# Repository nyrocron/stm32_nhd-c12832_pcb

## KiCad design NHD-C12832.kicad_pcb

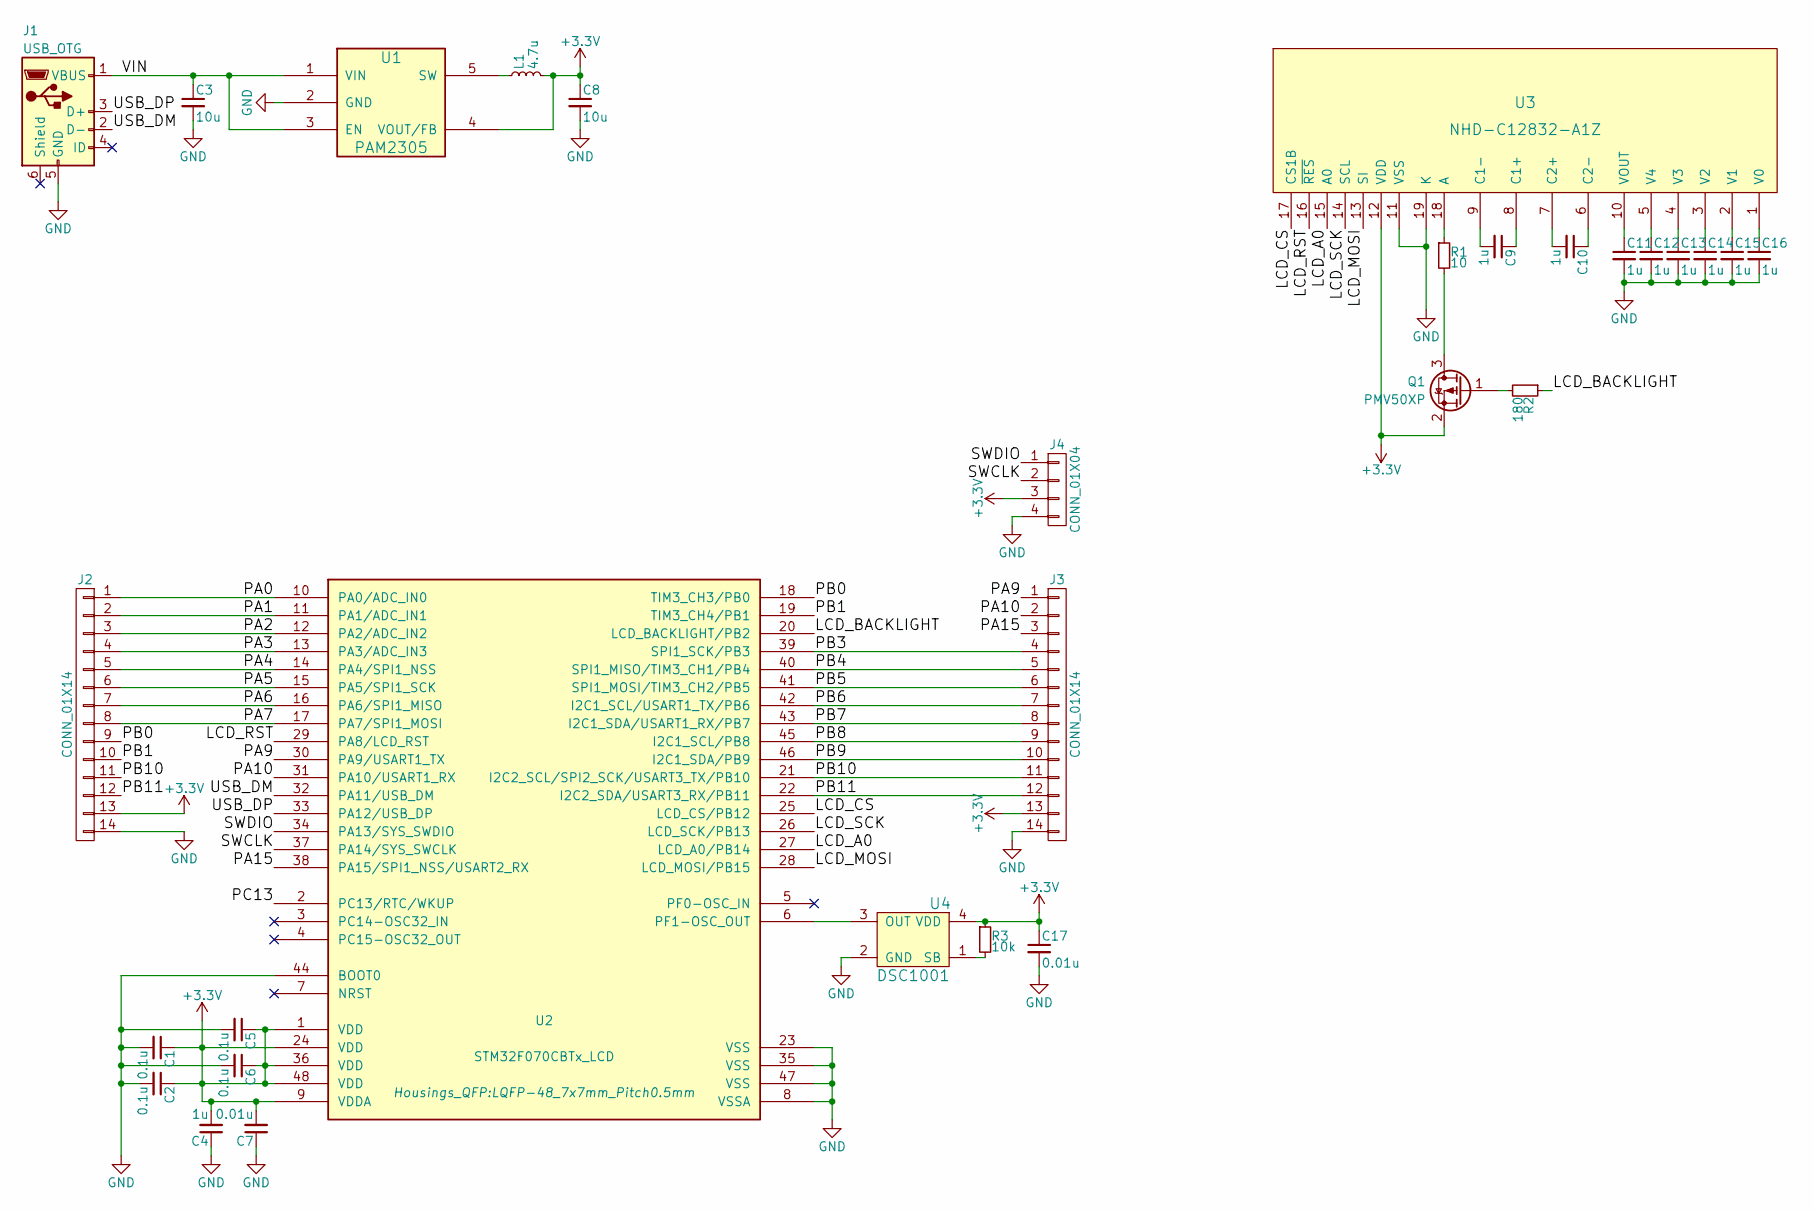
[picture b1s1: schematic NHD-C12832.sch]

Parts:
C1, C2, C5, C6: 0.1u; C_0603
C3, C8: 10u; C_0805
C4, C9, C10, C11, C12, C13, C14, C15, C16: 1u; C_0603
C7, C17: 0.01u; C_0603
J1: USB_OTG; USB_Micro-B_surface2
J2, J3: CONN_01X14; SOLDERPADS_14
J4: CONN_01X04; JST-SH_SM04B
L1: 4.7u; C_0805
Q1: PMV50XP; SOT-23
R1: 10; R_0603
R2: 180; R_0603
R3: 10k; R_0603
U1: PAM2305; SOT-23-5
U2: STM32F070CBTx_LCD; LQFP-48_7x7mm_Pitch0.5mm
U3: NHD-C12832-A1Z; NHD-C12832
U4: DSC1001; Crystal_SMD_5032-4pin_5.0x3.2mm

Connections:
+3V3: C1.1, C2.1, C4.2, C5.1, C6.1, C7.2, C8.1, C17.1, J2.13, J3.13, J4.3, L1.2, Q1.2 (S), R3.1, U1.4 (VOUT/FB), U2.1 (VDD), U2.9 (VDDA), U2.24 (VDD), U2.36 (VDD), U2.48 (VDD), U3.12 (VDD), U4.4 (VDD)
/LCD_A0: U2.27 (LCD_A0/PB14), U3.15 (A0)
/LCD_BACKLIGHT: R2.1, U2.20 (LCD_BACKLIGHT/PB2)
/LCD_CS: U2.25 (LCD_CS/PB12), U3.17 (CS1B)
/LCD_MOSI: U2.28 (LCD_MOSI/PB15), U3.13 (SI)
/LCD_RST: U2.29 (PA8/LCD_RST), U3.16 (~RES)
/LCD_SCK: U2.26 (LCD_SCK/PB13), U3.14 (SCL)
/PA0: J2.1, U2.10 (PA0/ADC_IN0)
/PA1: J2.2, U2.11 (PA1/ADC_IN1)
/PA2: J2.3, U2.12 (PA2/ADC_IN2)
/PA3: J2.4, U2.13 (PA3/ADC_IN3)
/PA4: J2.5, U2.14 (PA4/SPI1_NSS)
/PA5: J2.6, U2.15 (PA5/SPI1_SCK)
/PA6: J2.7, U2.16 (PA6/SPI1_MISO)
/PA7: J2.8, U2.17 (PA7/SPI1_MOSI)
/PA9: J3.1, U2.30 (PA9/USART1_TX)
/PA10: J3.2, U2.31 (PA10/USART1_RX)
/PA15: J3.3, U2.38 (PA15/SPI1_NSS/USART2_RX)
/PB0: J2.9, U2.18 (TIM3_CH3/PB0)
/PB1: J2.10, U2.19 (TIM3_CH4/PB1)
/PB3: J3.4, U2.39 (SPI1_SCK/PB3)
/PB4: J3.5, U2.40 (SPI1_MISO/TIM3_CH1/PB4)
/PB5: J3.6, U2.41 (SPI1_MOSI/TIM3_CH2/PB5)
/PB6: J3.7, U2.42 (I2C1_SCL/USART1_TX/PB6)
/PB7: J3.8, U2.43 (I2C1_SDA/USART1_RX/PB7)
/PB8: J3.9, U2.45 (I2C1_SCL/PB8)
/PB9: J3.10, U2.46 (I2C1_SDA/PB9)
/PB10: J2.11, J3.11, U2.21 (I2C2_SCL/SPI2_SCK/USART3_TX/PB10)
/PB11: J2.12, J3.12, U2.22 (I2C2_SDA/USART3_RX/PB11)
/SWCLK: J4.2, U2.37 (PA14/SYS_SWCLK)
/SWDIO: J4.1, U2.34 (PA13/SYS_SWDIO)
/USB_DM: J1.2 (D-), U2.32 (PA11/USB_DM)
/USB_DP: J1.3 (D+), U2.33 (PA12/USB_DP)
/VIN: C3.1, J1.1 (VBUS), U1.1 (VIN), U1.3 (EN)
GND: C1.2, C2.2, C3.2, C4.1, C5.2, C6.2, C7.1, C8.2, C11.2, C12.2, C13.2, C14.2, C15.2, C16.2, C17.2, J1.5 (GND), J2.14, J3.14, J4.4, U1.2 (GND), U2.8 (VSSA), U2.23 (VSS), U2.35 (VSS), U2.44 (BOOT0), U2.47 (VSS), U3.11 (VSS), U3.19 (K), U4.2 (GND)
unnamed: C9.1, U3.8 (C1+)
unnamed: C9.2, U3.9 (C1-)
unnamed: C10.1, U3.6 (C2-)
unnamed: C10.2, U3.7 (C2+)
unnamed: C11.1, U3.10 (VOUT)
unnamed: C12.1, U3.5 (V4)
unnamed: C13.1, U3.4 (V3)
unnamed: C14.1, U3.3 (V2)
unnamed: C15.1, U3.2 (V1)
unnamed: C16.1, U3.1 (V0)
unnamed: L1.1, U1.5 (SW)
unnamed: Q1.1 (G), R2.2
unnamed: Q1.3 (D), R1.2
unnamed: R1.1, U3.18 (A)
unnamed: R3.2, U4.1 (SB)
unnamed: U2.6 (PF1-OSC_OUT), U4.3 (OUT)

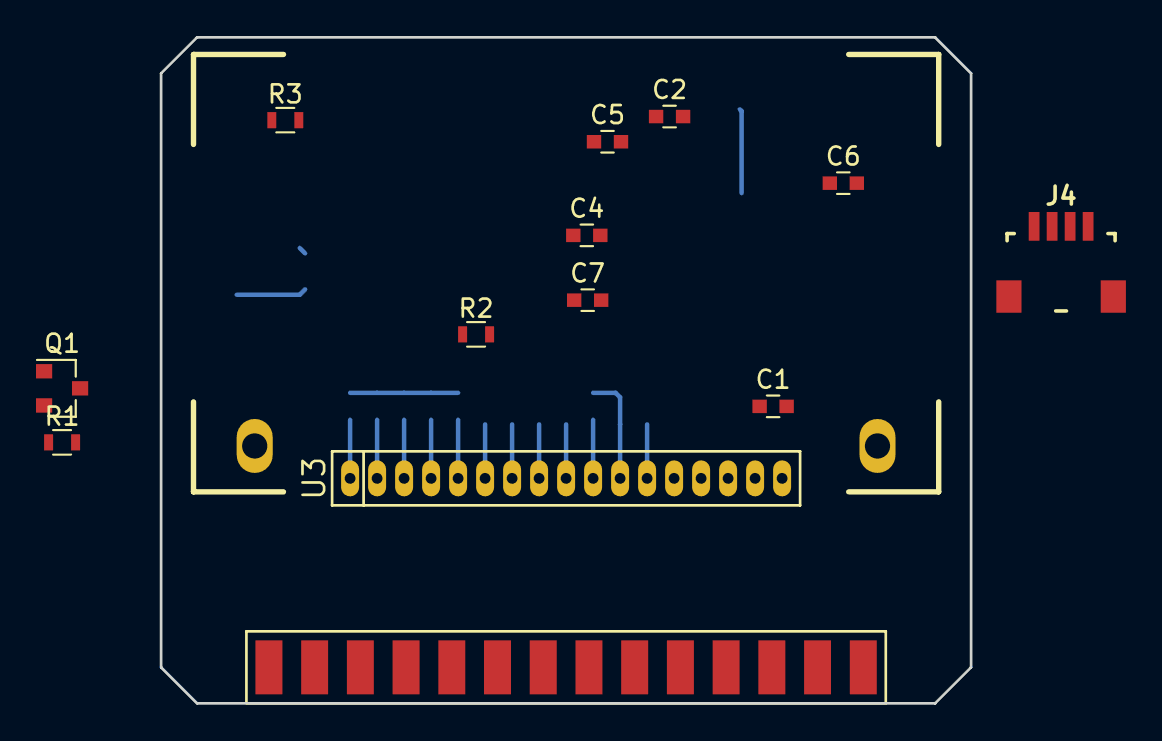
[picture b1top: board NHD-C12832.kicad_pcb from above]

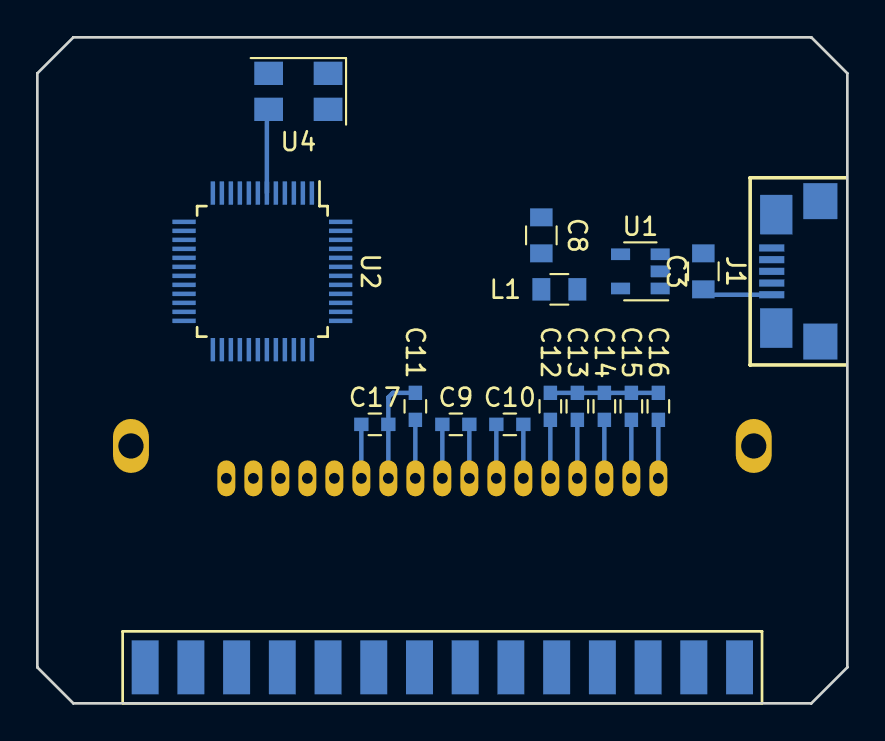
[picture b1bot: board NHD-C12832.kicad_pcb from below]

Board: 2 copper layers, 45.0 x 37.0 mm, 30 parts (17 on the bottom side), 51 nets.
